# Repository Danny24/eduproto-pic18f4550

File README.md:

# eduproto-pic18f4550
Este es un diseño funcional para la tarjeta que se usa en microcontroladores por el maestro Cornejo en CETI colomos.

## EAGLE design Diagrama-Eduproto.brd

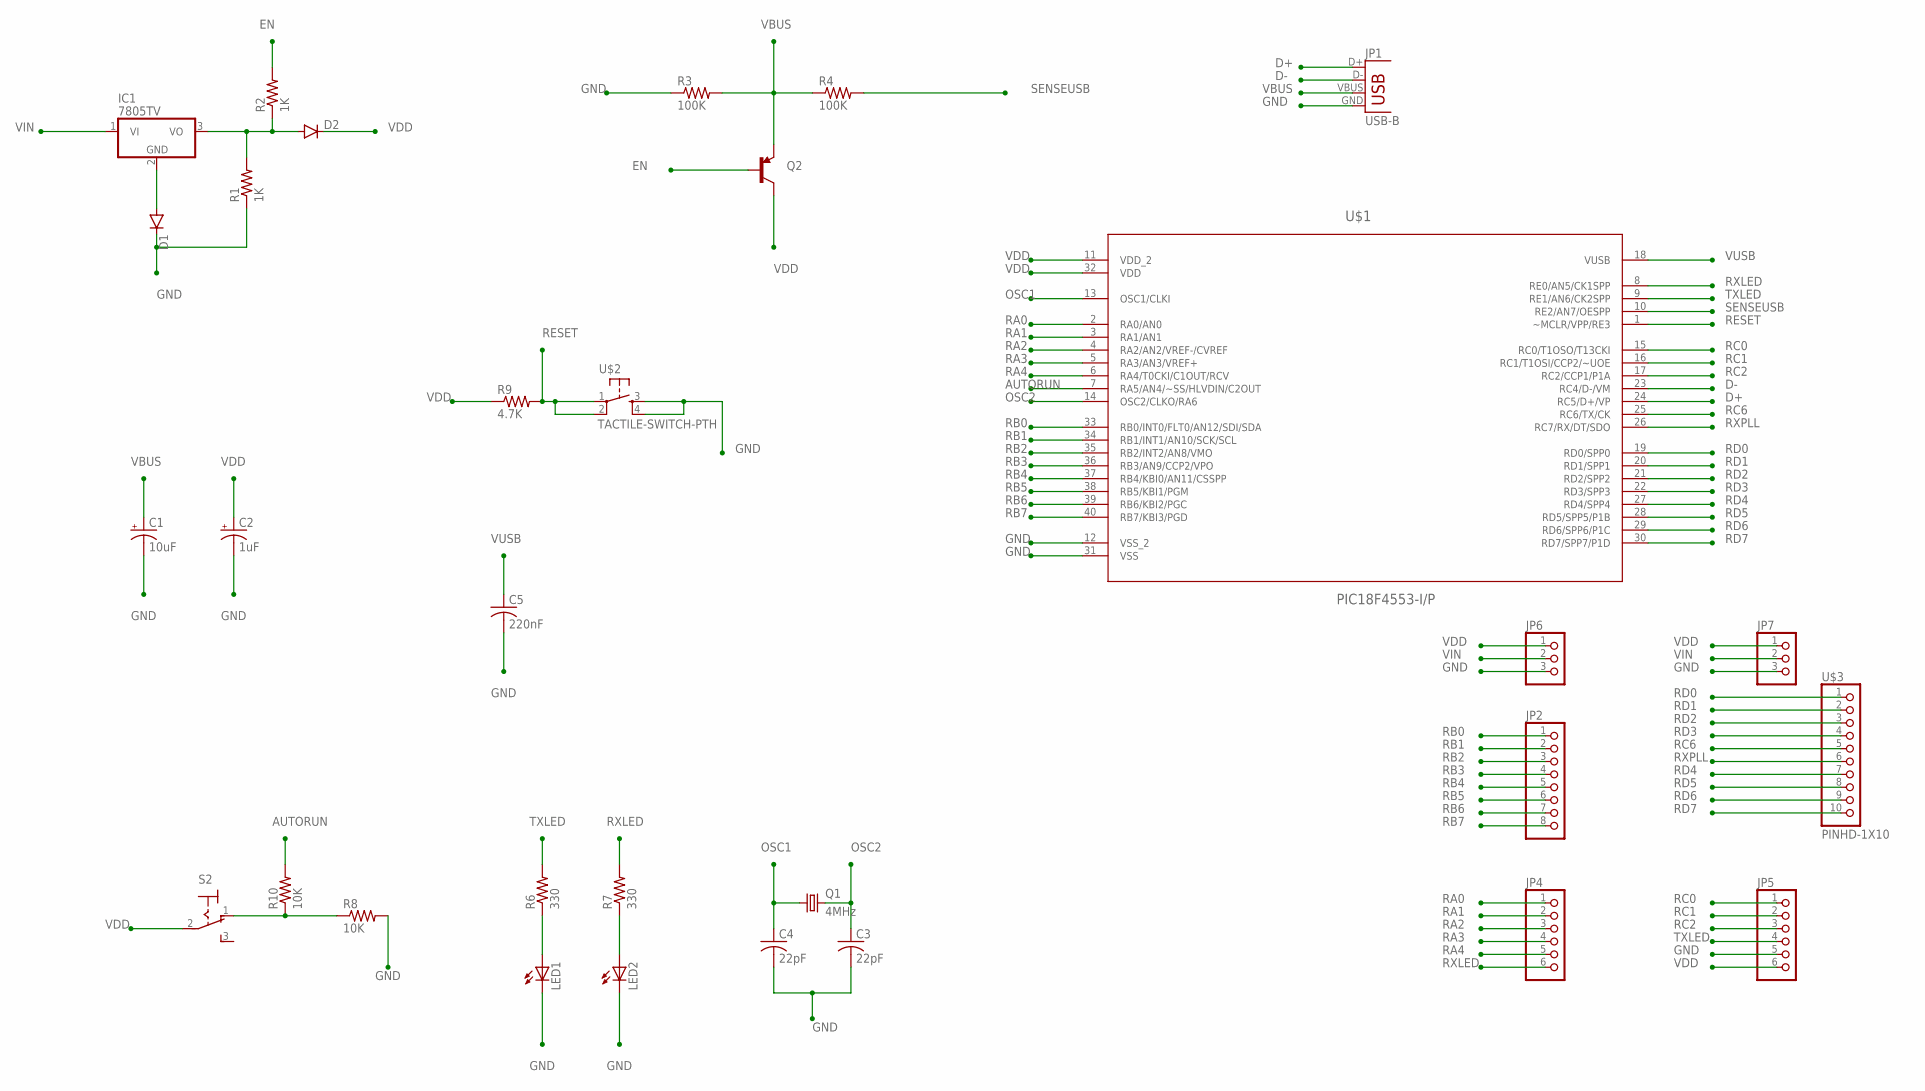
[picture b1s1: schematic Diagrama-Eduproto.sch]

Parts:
C1: 10uF; E2,5-6
C2: 1uF; E2,5-6
C3, C4: 22pF; C050-024X044
C5: 220nF; C075-042X103
D1, D2: DIODEPTH; DIODE-1N4001
IC1: 7805TV; TO220V
JP1: USB-B; USB-B-PTH
JP2: PINHD-1X8BIG; 1X08-BIG
JP4, JP5: PINHD-1X6; 1X06
JP6, JP7: PINHD-1X3; 1X03
LED1, LED2: LED5MM
Q1: 4MHz; HC49/S
Q2: TRANSISTOR_PNPTO92; TO-92
R1, R2: 1K; 0207/10
R3, R4: 100K; 0207/10
R6, R7: 330; 0207/10
R8, R10: 10K; 0207/10
R9: 4.7K; 0207/10
S2: M9040P
U$1: PIC18F4553-I/P; DIP254P1524X635-40
U$2: TACTILE-SWITCH-PTH; TAC-SWITCH-PTH
U$3: PINHD-1X10; 1X10-BIG

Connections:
AUTORUN: R10.2, U$1.7 (RA5/AN4/~SS/HLVDIN/C2OUT)
D+: JP1.D+, U$1.24 (RC5/D+/VP)
D-: JP1.D-, U$1.23 (RC4/D-/VM)
EN: Q2.2 (B), R2.2
GND: C1.-, C2.-, C3.2, C4.2, C5.2, D1.C, JP1.GND, JP5.5, JP6.3, JP7.3, LED1.K (C), LED2.K (C), R1.1, R3.1, R8.2, U$1.12 (VSS_2), U$1.31 (VSS), U$2.3, U$2.4
unnamed: D1.A, IC1.2 (GND)
unnamed: R8.1, R10.1, S2.1 (O)
unnamed: D2.A, IC1.3 (VO), R1.2, R2.1
unnamed: LED1.A, R6.1
unnamed: LED2.A, R7.1
OSC1: C4.1, Q1.1, U$1.13 (OSC1/CLKI)
OSC2: C3.1, Q1.2, U$1.14 (OSC2/CLKO/RA6)
RA0: JP4.1, U$1.2 (RA0/AN0)
RA1: JP4.2, U$1.3 (RA1/AN1)
RA2: JP4.3, U$1.4 (RA2/AN2/VREF-/CVREF)
RA3: JP4.4, U$1.5 (RA3/AN3/VREF+)
RA4: JP4.5, U$1.6 (RA4/T0CKI/C1OUT/RCV)
RB0: JP2.1, U$1.33 (RB0/INT0/FLT0/AN12/SDI/SDA)
RB1: JP2.2, U$1.34 (RB1/INT1/AN10/SCK/SCL)
RB2: JP2.3, U$1.35 (RB2/INT2/AN8/VMO)
RB3: JP2.4, U$1.36 (RB3/AN9/CCP2/VPO)
RB4: JP2.5, U$1.37 (RB4/KBI0/AN11/CSSPP)
RB5: JP2.6, U$1.38 (RB5/KBI1/PGM)
RB6: JP2.7, U$1.39 (RB6/KBI2/PGC)
RB7: JP2.8, U$1.40 (RB7/KBI3/PGD)
RC0: JP5.1, U$1.15 (RC0/T1OSO/T13CKI)
RC1: JP5.2, U$1.16 (RC1/T1OSI/CCP2/~UOE)
RC2: JP5.3, U$1.17 (RC2/CCP1/P1A)
RC6: U$1.25 (RC6/TX/CK), U$3.5
RD0: U$1.19 (RD0/SPP0), U$3.1
RD1: U$1.20 (RD1/SPP1), U$3.2
RD2: U$1.21 (RD2/SPP2), U$3.3
RD3: U$1.22 (RD3/SPP3), U$3.4
RD4: U$1.27 (RD4/SPP4), U$3.7
RD5: U$1.28 (RD5/SPP5/P1B), U$3.8
RD6: U$1.29 (RD6/SPP6/P1C), U$3.9
RD7: U$1.30 (RD7/SPP7/P1D), U$3.10
RESET: R9.2, U$1.1 (~MCLR/VPP/RE3), U$2.1, U$2.2
RXLED: JP4.6, R7.2, U$1.8 (RE0/AN5/CK1SPP)
RXPLL: U$1.26 (RC7/RX/DT/SDO), U$3.6
SENSEUSB: R4.2, U$1.10 (RE2/AN7/OESPP)
TXLED: JP5.4, R6.2, U$1.9 (RE1/AN6/CK2SPP)
VBUS: C1.+, JP1.VBUS, Q2.1 (E), R3.2, R4.1
VDD: C2.+, D2.C, JP5.6, JP6.1, JP7.1, Q2.3 (C), R9.1, S2.2, U$1.11 (VDD_2), U$1.32 (VDD)
VIN: IC1.1 (VI), JP6.2, JP7.2
VUSB: C5.1, U$1.18 (VUSB)

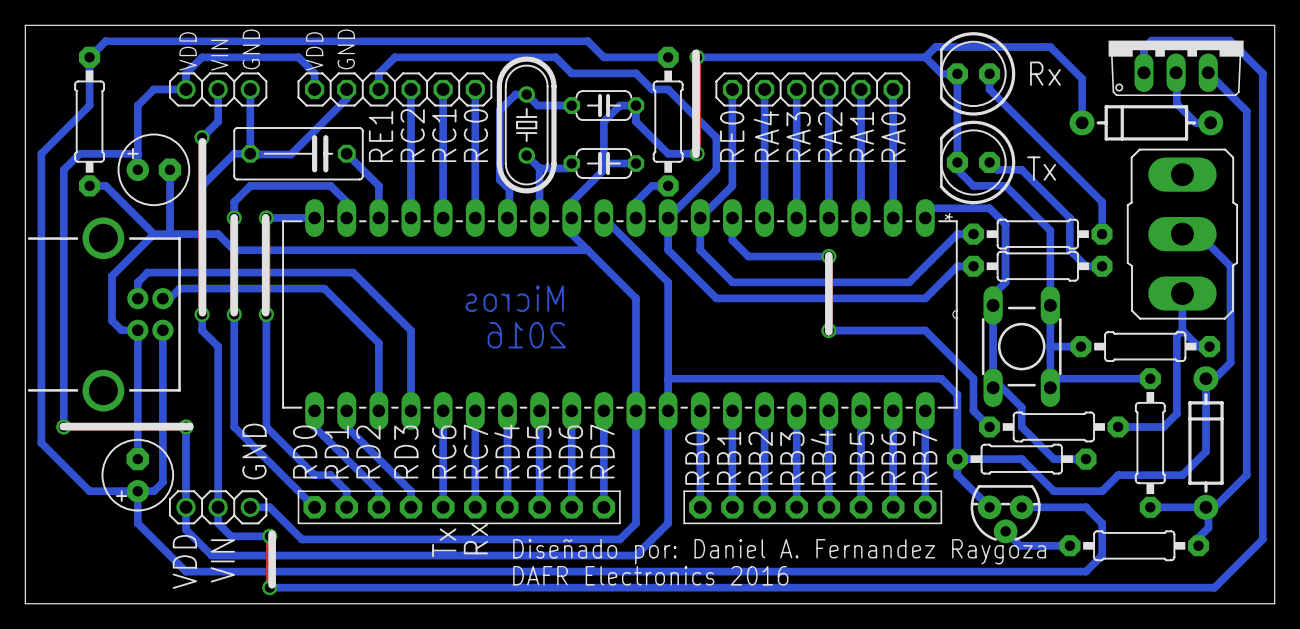
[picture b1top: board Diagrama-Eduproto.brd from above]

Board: 2 copper layers, 98.7 x 45.7 mm, 32 parts (0 on the bottom side), 46 nets.

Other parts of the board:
U$4: LOGO

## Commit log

2016-08-02 added eagle files
2018-12-04 new rev

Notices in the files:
parts and their libraries:
SparkFun-DiscreteSemi: Licensing: Creative Commons ShareAlike 4.0 International - https://creativecommons.org/licenses/by-sa/4.0
